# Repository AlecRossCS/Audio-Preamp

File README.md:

# Audio-Preamp
This is an analog audio preamplifier, designed on first principles as well as help from Small Signal Audio Design by Douglas Self, as well as applications notes from Rod Elliott. 

## Schematic
the schematic is listed in the project files, in many parts. [the pdf schematic is linked here](Audio_Preamp.pdf)

## Power Supply Design
The design for the power supply relies on an Input AC plug pack, anywhere between 12-25V input.

it is designed with some input protection from transient spikes of wall voltage, if the plug pack is poorly designed by a MOV. Effectively it is a half wave rectifier for each rail, and a virtual ground point.  Otherwise it is a fairly standard linear power supply, except that to reduce cost and part count, a input capacitance is obtained through a capacitance multiplier. the only disadvantage is that it cannot help source higher currents, but that is not needed on a preamplifier as well as being mitigated by a high output capacitance. 

## Other Design elements

The rest of the design is fairly lengthy, and involves several larger elements taken from basic principles. The input is a standard RCA audio jack, as it is an easier connection and has better noise characteristics than a balanced input. the controls follow with a baxendall tonal control, and then a baxendall volume control. All of this is designed to be very low noise (-90DB) and high fidelity all analog preamp. 

## Hardware layout

This board needed to be relatively space efficient, and total space is one factor which influences cost of production. so this is designed as a 50x80 mm  4 layer board, which should make a favorable production cost. as this is fiarly small and lower power another cost saver is it only needs 1 oz copper, not 2 oz copper. Another point for production is that almost all components are SMD, thus decreases cost of assembly. 

overall mockup:

## version 2
This version has RCA out, but V2 may have balanced output as well as active crossovers.

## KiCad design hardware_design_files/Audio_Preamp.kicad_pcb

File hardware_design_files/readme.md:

# Hardware Design File Section
all schematics created using Kicad

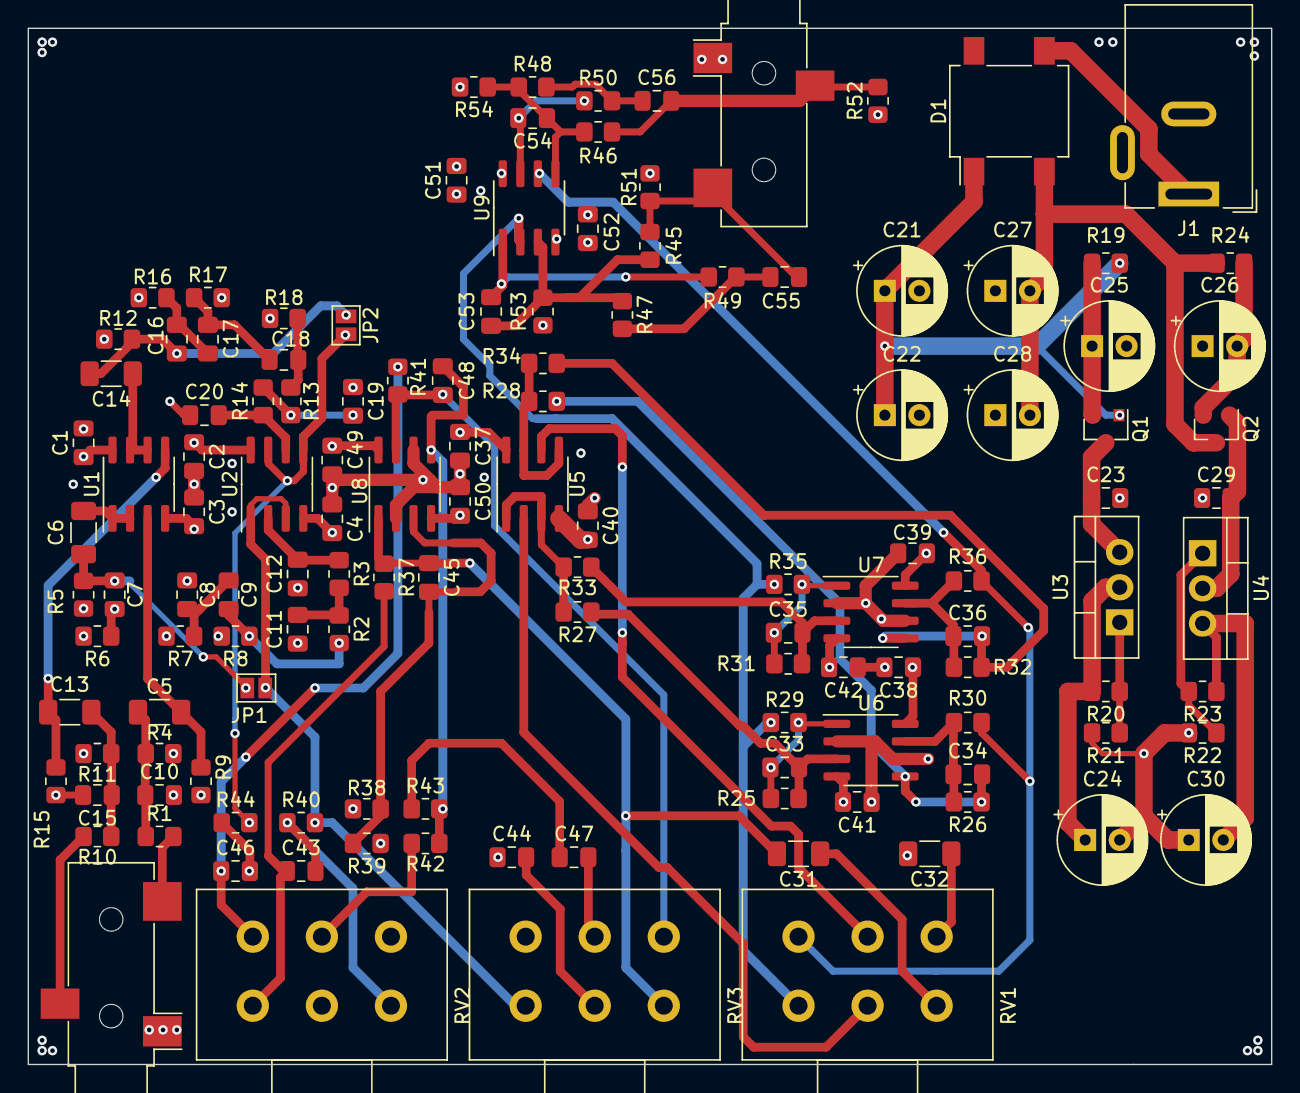
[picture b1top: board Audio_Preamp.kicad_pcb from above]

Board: 4 copper layers, 90.0 x 75.0 mm, 130 parts (0 on the bottom side), 72 nets.

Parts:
C1, C2, C3, C4, C7, C8, C9, C16, C17, C18, C37, C38, C39, C40, C41, C42, C49, C50, C51, C52: 470n; C_0805_2012Metric_Pad1.18x1.45mm_HandSolder
C5, C6, C13, C14, C31, C32: 10u; C_1206_3216Metric_Pad1.33x1.80mm_HandSolder
C10, C15, C33, C34, C35, C36: 100p; C_0805_2012Metric_Pad1.18x1.45mm_HandSolder
C11, C19: 4.4n; C_0805_2012Metric_Pad1.18x1.45mm_HandSolder
C12, C20: 2.2n; C_0805_2012Metric_Pad1.18x1.45mm_HandSolder
C21, C22, C24, C25, C26, C27, C28, C30: 100u; CP_Radial_D6.3mm_P2.50mm
C23, C29, C43, C46: 100n; C_0805_2012Metric_Pad1.18x1.45mm_HandSolder
C44, C47: 4.7n; C_0805_2012Metric_Pad1.18x1.45mm_HandSolder
C45, C48: 22p; C_0805_2012Metric_Pad1.18x1.45mm_HandSolder
C53, C54: 47p; C_0805_2012Metric_Pad1.18x1.45mm_HandSolder
C55, C56: 100u; C_0805_2012Metric_Pad1.18x1.45mm_HandSolder
D1: D_Bridge_+-AA; Diode_Bridge_Vishay_DFS
J1: Barrel_Jack; BarrelJack_Wuerth_6941xx301002
J2, J3: AudioJack3; Jack_3.5mm_CUI_SJ-3523-SMT_Horizontal
JP1, JP2: SolderJumper-2_P1.3mm_Open_Pad1.0x1.5mm
Q1: Q_NPN_CBE; SOT-23
Q2: Q_PNP_CBE; SOT-23
R1, R10: 100; R_0805_2012Metric_Pad1.20x1.40mm_HandSolder
R2, R3, R13, R14, R27, R28, R33, R34: 1k; R_0805_2012Metric_Pad1.20x1.40mm_HandSolder
R4, R11: 220k; R_0805_2012Metric_Pad1.20x1.40mm_HandSolder
R5, R12, R38, R42, R51, R52: 22k; R_0805_2012Metric_Pad1.20x1.40mm_HandSolder
R6, R7, R16, R17, R37, R40, R41, R44, R53, R54: 4.7k; R_0805_2012Metric_Pad1.20x1.40mm_HandSolder
R8, R18: 82k; R_0805_2012Metric_Pad1.20x1.40mm_HandSolder
R9, R15, R47, R48: 100k; R_0805_2012Metric_Pad1.20x1.40mm_HandSolder
R19, R24: 1M; R_0805_2012Metric_Pad1.20x1.40mm_HandSolder
R20, R23: 120; R_0805_2012Metric_Pad1.20x1.40mm_HandSolder
R21, R22: 1.32k; R_0805_2012Metric_Pad1.20x1.40mm_HandSolder
R25, R26, R31, R32: 3.3k; R_0805_2012Metric_Pad1.20x1.40mm_HandSolder
R29, R30, R35, R36: 10; R_0805_2012Metric_Pad1.20x1.40mm_HandSolder
R39, R43: 9.1k; R_0805_2012Metric_Pad1.20x1.40mm_HandSolder
R45, R46: 10k; R_0805_2012Metric_Pad1.20x1.40mm_HandSolder
R49, R50: 68; R_0805_2012Metric_Pad1.20x1.40mm_HandSolder
RV1: 5k; Potentiometer_Alps_RK163_Dual_Horizontal
RV2, RV3: 10k; Potentiometer_Alps_RK163_Dual_Horizontal
U1, U2, U5, U6, U7, U8, U9: NE5532; SOIC-8_3.9x4.9mm_P1.27mm
U3: LM317_TO-220; TO-220-3_Vertical
U4: LM337_TO220; TO-220-3_Vertical

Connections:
+15V: C1.1, C2.1, C24.1, C37.1, C38.1, C39.1, C49.1, C51.1, R20.2, U1.8, U2.8, U3.2, U5.8, U6.8, U7.8, U8.8, U9.8
-15V: C3.2, C4.2, C30.2, C40.2, C41.2, C42.2, C50.2, C52.2, R23.1, U1.4, U2.4, U4.3, U5.4, U6.4, U7.4, U8.4, U9.4
/Audio_Input/Left: J2.T, R1.2
/Audio_Input/Right: J2.R, R10.2
/Power/In+: D1.3, J1.1
/Power/Neg: C27.2, C28.2, D1.2, Q2.3, R24.2
/Tone Control/LAudio: JP1.2, R40.2, RV3.1, U2.1, U2.3
/Tone Control/RAudio: JP2.2, R44.2, RV3.4, U2.5, U2.7
/Volume_Control/L: C31.2, C45.1, R37.1, RV3.3, U8.1
/Volume_Control/LV: R29.1, R35.1, RV1.1, U9.2
/Volume_Control/R: C32.2, C48.1, R41.1, RV3.6, U8.7
/Volume_Control/RV: R30.1, R36.1, RV1.4, U9.6
GND: C1.2, C2.2, C3.1, C4.1, C10.2, C11.1, C12.1, C15.2, C19.1, C20.1, C21.2, C22.2, C23.2, C24.2, C25.2, C26.1, C27.1, C28.1, C29.1, C30.1, C37.2, C38.2, C39.2, C40.1, C41.1, C42.1, C49.2, C50.1, C51.2, C52.1, J1.2, J2.S, J3.S, R4.2, R5.2, R6.2, R7.2, R8.2, R9.2, R11.2, R12.2, R15.2, R16.2, R17.2, R18.2, R21.2, R22.2, R51.1, R52.1, R53.2, R54.2, U6.2, U6.6, U7.2, U7.6, U8.2, U8.6
unnamed: C5.2, R9.1, U1.3
unnamed: C6.1, U1.1, U1.2
unnamed: C6.2, C7.2, JP1.1, R5.1
unnamed: C7.1, C8.2, R6.1
unnamed: C8.1, C9.2, R7.1
unnamed: C9.1, R2.2, R8.1
unnamed: C5.1, C10.1, R1.1, R4.1
unnamed: C11.2, R2.1, R3.2
unnamed: C12.2, R3.1, U2.2
unnamed: C13.1, C15.1, R10.1, R11.1
unnamed: C13.2, R15.1, U1.5
unnamed: C14.1, U1.6, U1.7
unnamed: C14.2, C16.2, JP2.1, R12.1
unnamed: C16.1, C17.2, R16.1
unnamed: C17.1, C18.2, R17.1
unnamed: C18.1, R13.2, R18.1
unnamed: C19.2, R13.1, R14.2
unnamed: C20.2, R14.1, U2.6
unnamed: C21.1, C22.1, D1.1, Q1.1, R19.1
unnamed: C23.1, Q1.3, U3.3
unnamed: C25.1, Q1.2, R19.2
unnamed: C26.2, Q2.2, R24.1
unnamed: C29.2, Q2.1, U4.2
unnamed: C31.1, RV1.3
unnamed: C32.1, RV1.6
unnamed: C33.1, R25.2, R29.2, U6.1
unnamed: C33.2, R25.1, R27.1, U6.3
unnamed: C34.1, R26.2, R30.2, U6.7
unnamed: C34.2, R26.1, R28.1, U6.5
unnamed: C35.1, R31.2, R35.2, U7.1
unnamed: C35.2, R31.1, R33.1, U7.3
unnamed: C36.1, R32.2, R36.2, U7.7
unnamed: C36.2, R32.1, R34.1, U7.5
unnamed: C43.1, R37.2, RV2.1
unnamed: C43.2, R40.1, RV2.3
unnamed: C44.1, R39.1
unnamed: C44.2, RV3.2
unnamed: C45.2, R38.1, R39.2, U8.3
unnamed: C46.1, R41.2, RV2.4
unnamed: C46.2, R44.1, RV2.6
unnamed: C47.1, R43.1
unnamed: C47.2, RV3.5
unnamed: C48.2, R42.1, R43.2, U8.5
unnamed: C53.1, R45.1, R47.1, R53.1, U9.3
unnamed: C53.2, R49.1, U9.1
unnamed: C54.1, R46.1, R48.1, R54.1, U9.5
unnamed: C54.2, R50.1, U9.7
unnamed: C55.1, R47.2, R49.2
unnamed: C55.2, J3.T, R45.2, R51.2
unnamed: C56.1, R48.2, R50.2
unnamed: C56.2, J3.R, R46.2, R52.2
unnamed: R20.1, R21.1, U3.1
unnamed: R22.1, R23.2, U4.1
unnamed: R27.2, R33.2, U5.1, U5.3
unnamed: R28.2, R34.2, U5.5, U5.7
unnamed: R38.2, RV2.2
unnamed: R42.2, RV2.5
unnamed: RV1.2, U5.2
unnamed: RV1.5, U5.6

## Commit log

2021-10-05 Create hardware_design_files
2021-10-07 Update README.md
    typo
